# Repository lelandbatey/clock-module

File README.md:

Clock-module
============

This repo contains PCB designs for the first component of Ben Eater's
educational 8-bit CPU, the clock module. You can [watch Mr. Eaters *fantastic*
series on designing and building this CPU on his Youtube
channel.](https://www.youtube.com/user/eaterbc/videos)

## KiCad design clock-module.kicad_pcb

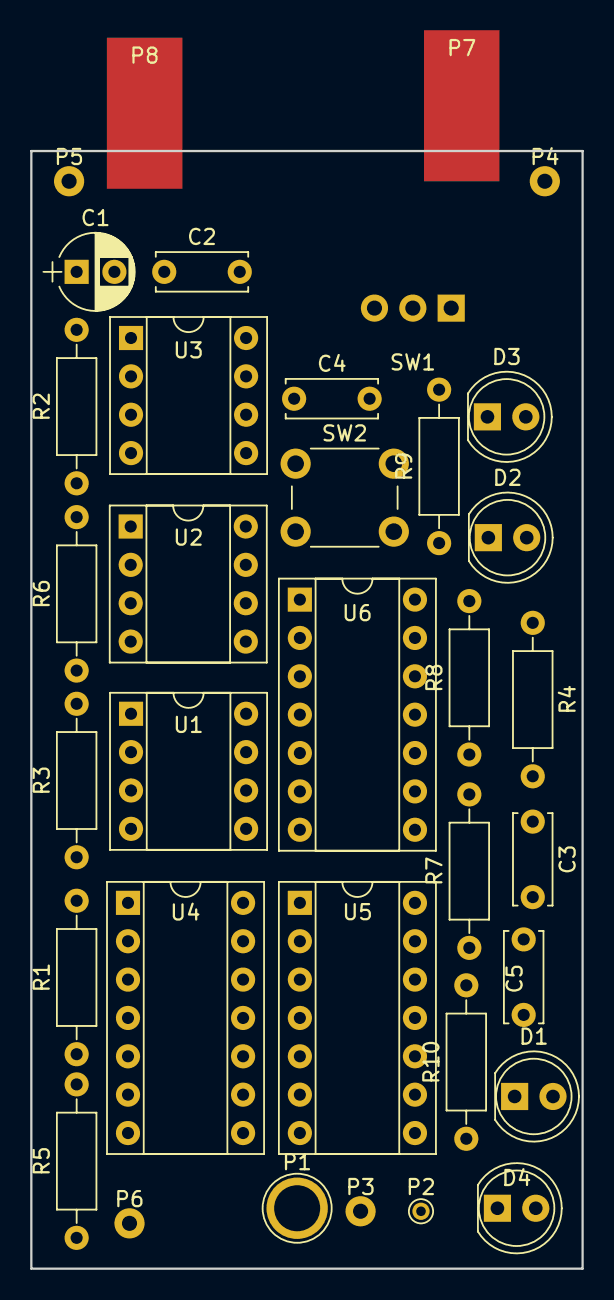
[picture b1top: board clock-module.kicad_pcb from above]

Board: 2 copper layers, 36.5 x 74.0 mm, 35 parts (0 on the bottom side), 25 nets, no tracks yet.

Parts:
C1: 1uf; CP_Radial_D5.0mm_P2.50mm
C2, C3, C4: 0.01uf; C_Disc_D6.0mm_W2.5mm_P5.00mm
C5: 0.1uf; C_Disc_D6.0mm_W2.5mm_P5.00mm
D1, D2, D3, D4: LED; LED_D5.0mm
P1: CONN_01X01; 1pin
P2: CONN_01X01; PINTST
P3, P4, P5, P6: CONN_01X01; test_pin_single_hole
P7, P8: CONN_01X01; SolderWirePad_single_SMD_5x10mm
R1, R2, R3, R6: 1k; R_Axial_DIN0207_L6.3mm_D2.5mm_P10.16mm_Horizontal
R4: 1M; R_Axial_DIN0207_L6.3mm_D2.5mm_P10.16mm_Horizontal
R5: 100k; R_Axial_DIN0207_L6.3mm_D2.5mm_P10.16mm_Horizontal
R7, R8, R9, R10: 220; R_Axial_DIN0207_L6.3mm_D2.5mm_P10.16mm_Horizontal
SW1: SW_SPDT; SPDT_L15mm_W8mm
SW2: SW_SPST; SW_PUSH_6mm
U1, U2, U3: LM555N; DIP-8_W7.62mm_Socket
U4: 74LS04; DIP-14_W7.62mm_Socket
U5: 74LS08; DIP-14_W7.62mm_Socket
U6: 74LS32; DIP-14_W7.62mm_Socket

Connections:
+5V: P4.1, P7.1, R3.1, R4.1, R6.1, SW2.1, U1.4, U1.8, U2.4, U2.8, U3.8, U4.14, U5.14, U6.14
GND: C1.2, C2.2, C3.2, C4.2, C5.1, P5.1, P8.1, R1.1, R2.2, R7.1, R8.1, R9.1, R10.1, SW1.2, U1.1, U2.1, U3.1, U3.6, U4.7, U5.7, U6.7
unnamed: C1.1, R5.2, U1.2, U1.6
unnamed: C2.1, U1.5
unnamed: C3.1, U2.5
unnamed: C4.1, U3.5
unnamed: C5.2, R4.2, U2.6, U2.7
unnamed: D1.1, R7.2
unnamed: D1.2, U1.3, U5.1
unnamed: D2.1, R8.2
unnamed: D2.2, U2.3, U5.5
unnamed: D3.1, R9.2
unnamed: D3.2, U3.3, U4.1, U5.2
unnamed: D4.1, R10.2
unnamed: D4.2, P1.1, P2.1, P3.1, U5.8
unnamed: P6.1, U4.3
unnamed: R1.2, SW1.1, U3.2
unnamed: R2.1, SW1.3, U3.4
unnamed: R3.2, SW2.2, U2.2
unnamed: R5.1, R6.2, U1.7
unnamed: U4.2, U5.4
unnamed: U4.4, U5.10
unnamed: U5.3, U6.1
unnamed: U5.6, U6.2
unnamed: U5.9, U6.3

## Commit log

2017-02-28 Initial commit, adding existing files
2017-02-28 Add README with PCB image
2017-03-01 Improve pad clearences, aligator clip improvements
2017-03-26 Fix bug in board layout
